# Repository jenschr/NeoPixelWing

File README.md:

# NeoPixelWing
Simple FeatherWing for controlling two strands of NeoPixels. It's basically just a 2-channel level shifter with two Potmeters, but very useful for lighting projects.

If you want to create your own FeatherWing, feel fre to use the bare project that I setup this project from as a verified starting point: https://github.com/jenschr/FeatherWing Big thanks to Adafruit for making the Feather format!

Pictures of the finished board and usage on my blog: https://flashgamer.com/blog/comments/neopixel-wing-for-feather

Please note: The Project is in Kicad 5 format. If you still use kicad 4 - I highly recommend swapping! V5 is better than V4 in so many ways.

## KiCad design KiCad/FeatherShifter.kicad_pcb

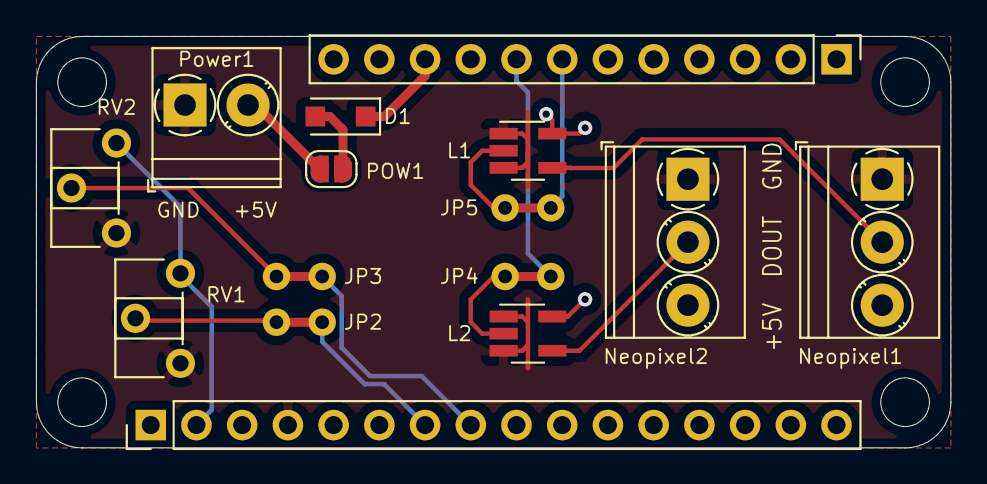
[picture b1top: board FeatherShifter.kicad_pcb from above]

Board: 2 copper layers, 50.8 x 22.9 mm, 19 parts (0 on the bottom side), 15 nets.

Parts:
D1: D; D_SOD-123F
H1, H2, H3, H4: MountingHole; MountingHole_2.7mm_M2.5
J1: Conn_01x12; PinHeader_1x12_P2.54mm_Vertical
J2: Conn_01x16; PinHeader_1x16_P2.54mm_Vertical
JP2, JP3, JP4, JP5: Jumper; Jumper2PinTHT
L1, L2: 74AHCT1G125; SOT-23-5_HandSoldering
Neopixel1, Neopixel2: Screw_Terminal_01x03; TerminalBlock_Phoenix_PT-1,5-3-3.5-H_1x03_P3.50mm_Horizontal
POW1: SolderJumper_2_Open; SolderJumper-2_P1.3mm_Open_RoundedPad1.0x1.5mm
Power1: Screw_Terminal_01x02; TerminalBlock_Phoenix_PT-1,5-2-3.5-H_1x02_P3.50mm_Horizontal
RV1, RV2: R_POT; Potentiometer_ACP_CA6-H2,5_Horizontal

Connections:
+3V3: J2.2, RV1.3, RV2.3
+5V: L1.5, L2.5, Neopixel1.3, Neopixel2.3, POW1.1, Power1.2
/a2: J2.7, JP2.2
/a3: J2.8, JP3.2
/d11: J1.7, JP5.2
/d12: J1.8, JP4.2
/usb: D1.1, J1.10
GND: J2.4, L1.1, L1.3, L2.1, L2.3, Neopixel1.1, Neopixel2.1, Power1.1, RV1.1, RV2.1
unnamed: D1.2, POW1.2
unnamed: JP2.1, RV1.2
unnamed: JP3.1, RV2.2
unnamed: JP4.1, L2.2
unnamed: JP5.1, L1.2
unnamed: L1.4, Neopixel1.2
unnamed: L2.4, Neopixel2.2

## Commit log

2019-07-26 First verified version of the FeatherWing
